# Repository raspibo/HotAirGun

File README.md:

HotAirGun
===================== 
Hot Air Solder station project
3D models for case

Project preview
=====================

<table>
<tr>
<td>

</td><td>

</td><td>

</td>
</tr>
<tr>
<td>

</td><td>

</td><td>

</td>
</tr>
</table>

License and copyright
=====================

Copyright 2017-2018 sandroxGH infomsystemsrl@gmail.com, RaspiBO info@raspibo.org

Licensed under the Apache License, Version 2.0 (the "License"); you may not use this file except in compliance with the License. You may obtain a copy of the License at http://www.apache.org/licenses/LICENSE-2.0

Unless required by applicable law or agreed to in writing, software distributed under the License is distributed on an "AS IS" BASIS, WITHOUT WARRANTIES OR CONDITIONS OF ANY KIND, either express or implied. See the License for the specific language governing permissions and limitations under the License.

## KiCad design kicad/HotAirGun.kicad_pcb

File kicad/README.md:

# Avvertenza sul caricamento dei simboli
All'apertura dello schema kicad può richiedere di sostituire i simboli dei componenti come se si riferissero a librerie obsolete.

E' consigliabile annullare l'operazione in modo che venga caricato il simbolo presente nel file cache delle librerie.

Schema preview
=====================

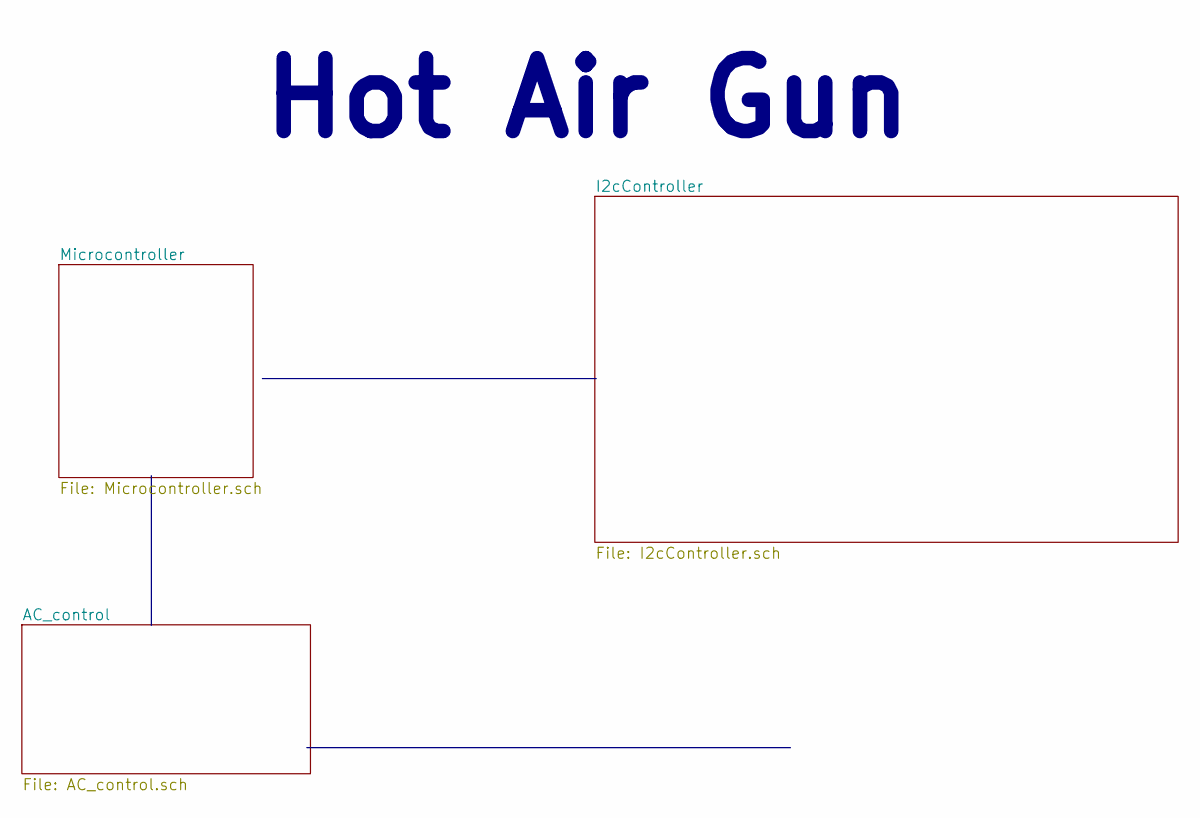
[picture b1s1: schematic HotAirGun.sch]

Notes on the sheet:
Hot Air Gun

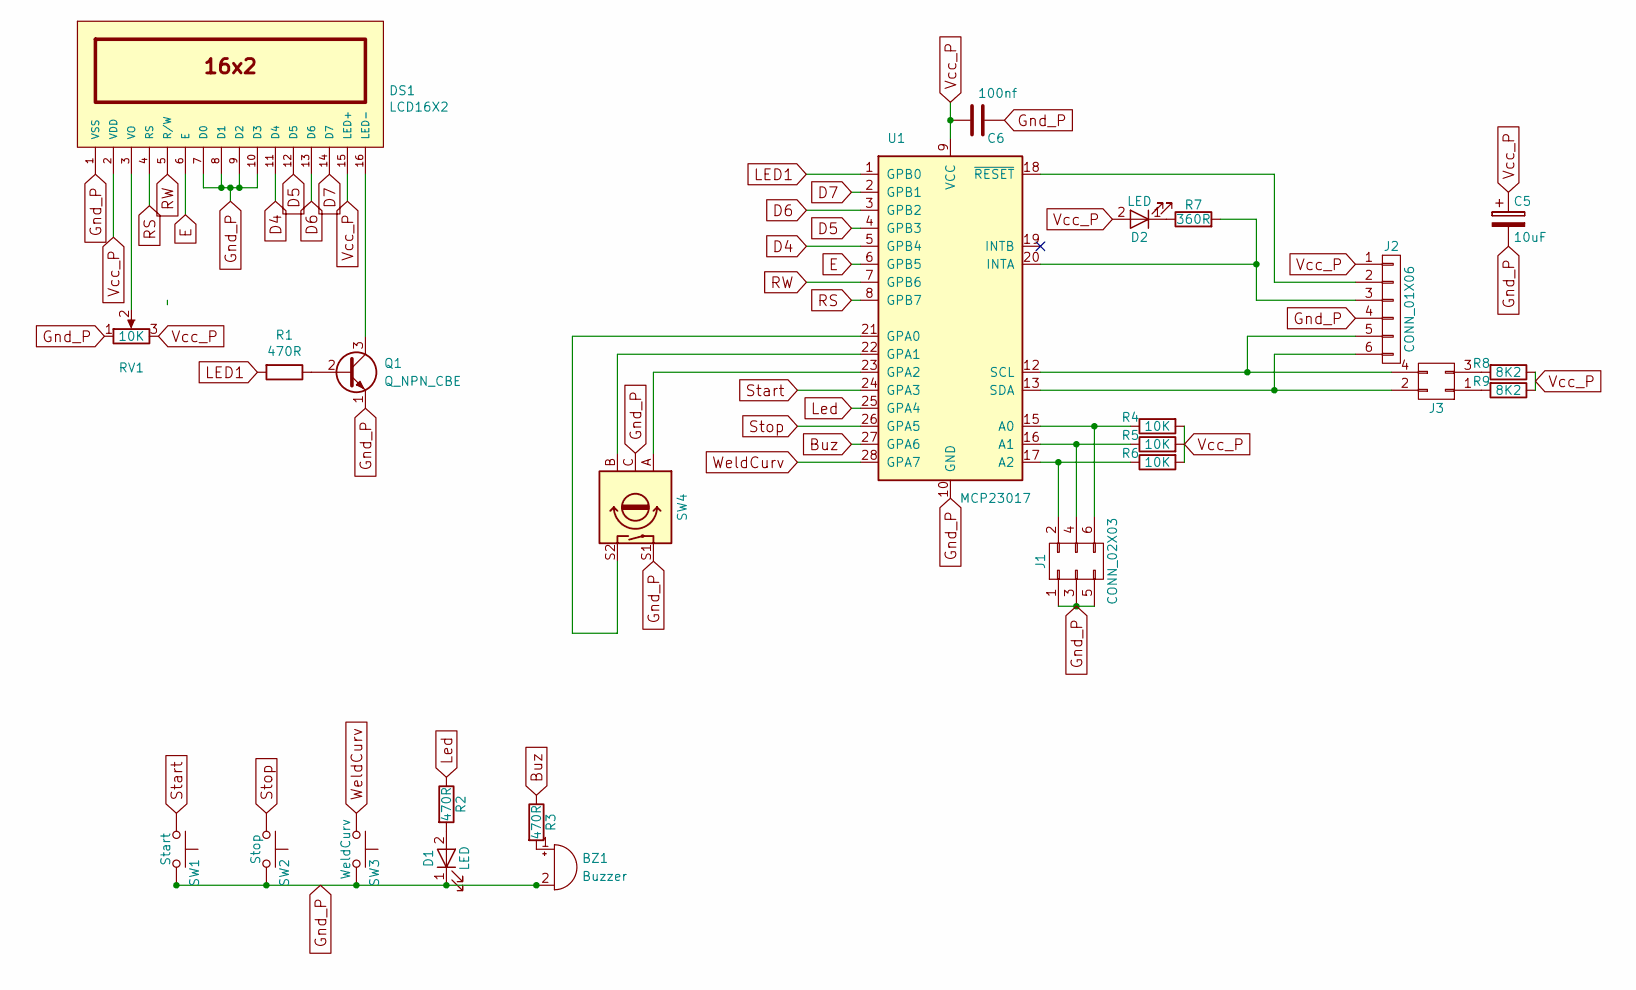
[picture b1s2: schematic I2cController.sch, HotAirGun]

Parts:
BZ1: Buzzer; Buzzer_12x9.5RM7.6
C5: 10uF; CP_Radial_D10.0mm_P5.00mm
C6: 100nf; C_0603_HandSoldering
D1, D2: LED; LED-5MM
DS1: LCD16X2; WC1602A
J1: CONN_02X03; Pin_Header_Straight_2x03
J2: CONN_01X06; Pin_Header_Straight_1x06
J3: CONN_02X02; Pin_Header_Straight_2x02
Q1: Q_NPN_CBE; TO-92_Rugged_Reverse
R1: 470R; R3
R2, R3: 470R; R_0603_HandSoldering
R4, R5, R6: 10K; R_0603_HandSoldering
R7: 360R; R_0603_HandSoldering
R8, R9: 8K2; R_0603_HandSoldering
RV1: 10K; Potentiometer_VishaySpectrol-Econtrim-Type36M
SW1: Start; SW_PUSH_SMALL
SW2: Stop; SW_PUSH_SMALL
SW3: WeldCurv; SW_PUSH_SMALL
SW4: Rotary_Encoder_Switch_V2; RotaryEncoder_Alps_EC11E-Switch_Vertical_H20mm
U1: MCP23017; DIP-28_W7.62mm_LongPads

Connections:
Buz: R3.1, U1.27 (GPA6)
D4: DS1.11 (D4), U1.5 (GPB4)
D5: DS1.12 (D5), U1.4 (GPB3)
D6: DS1.13 (D6), U1.3 (GPB2)
D7: DS1.14 (D7), U1.2 (GPB1)
E: DS1.6 (E), U1.6 (GPB5)
Gnd_P: BZ1.2 (+), C5.2, C6.1, D1.1 (K), DS1.1 (VSS), DS1.7 (D0), DS1.8 (D1), DS1.9 (D2), DS1.10 (D3), J1.1, J1.3, J1.5, J2.4, Q1.1 (E), RV1.1, SW1.2, SW2.2, SW3.2, SW4.C, SW4.S1, U1.10 (GND)
LED1: R1.2, U1.1 (GPB0)
Led: R2.1, U1.25 (GPA4)
unnamed: BZ1.1 (-), R3.2
unnamed: D1.2 (A), R2.2
unnamed: D2.1 (K), R7.1
unnamed: DS1.3 (VO), RV1.2
unnamed: DS1.16 (LED-), Q1.3 (C)
unnamed: J1.2, R6.1, U1.17 (A2)
unnamed: J1.4, R5.1, U1.16 (A1)
unnamed: J1.6, R4.1, U1.15 (A0)
unnamed: J2.2, U1.18 (~RESET)
unnamed: J2.3, R7.2, U1.20 (INTA)
unnamed: J2.5, J3.4, U1.12 (SCL)
unnamed: J2.6, J3.2, U1.13 (SDA)
unnamed: J3.1, R9.2
unnamed: J3.3, R8.2
unnamed: Q1.2 (B), R1.1
unnamed: SW4.A, U1.23 (GPA2)
unnamed: SW4.B, U1.22 (GPA1)
unnamed: SW4.S2, U1.21 (GPA0)
RS: DS1.4 (RS), U1.8 (GPB7)
RW: DS1.5 (R/W), U1.7 (GPB6)
Start: SW1.1, U1.24 (GPA3)
Stop: SW2.1, U1.26 (GPA5)
Vcc_P: C5.1, C6.2, D2.2 (A), DS1.2 (VDD), DS1.15 (LED+), J2.1, R4.2, R5.2, R6.2, R8.1, R9.1, RV1.3, U1.9 (VCC)
WeldCurv: SW3.1, U1.28 (GPA7)

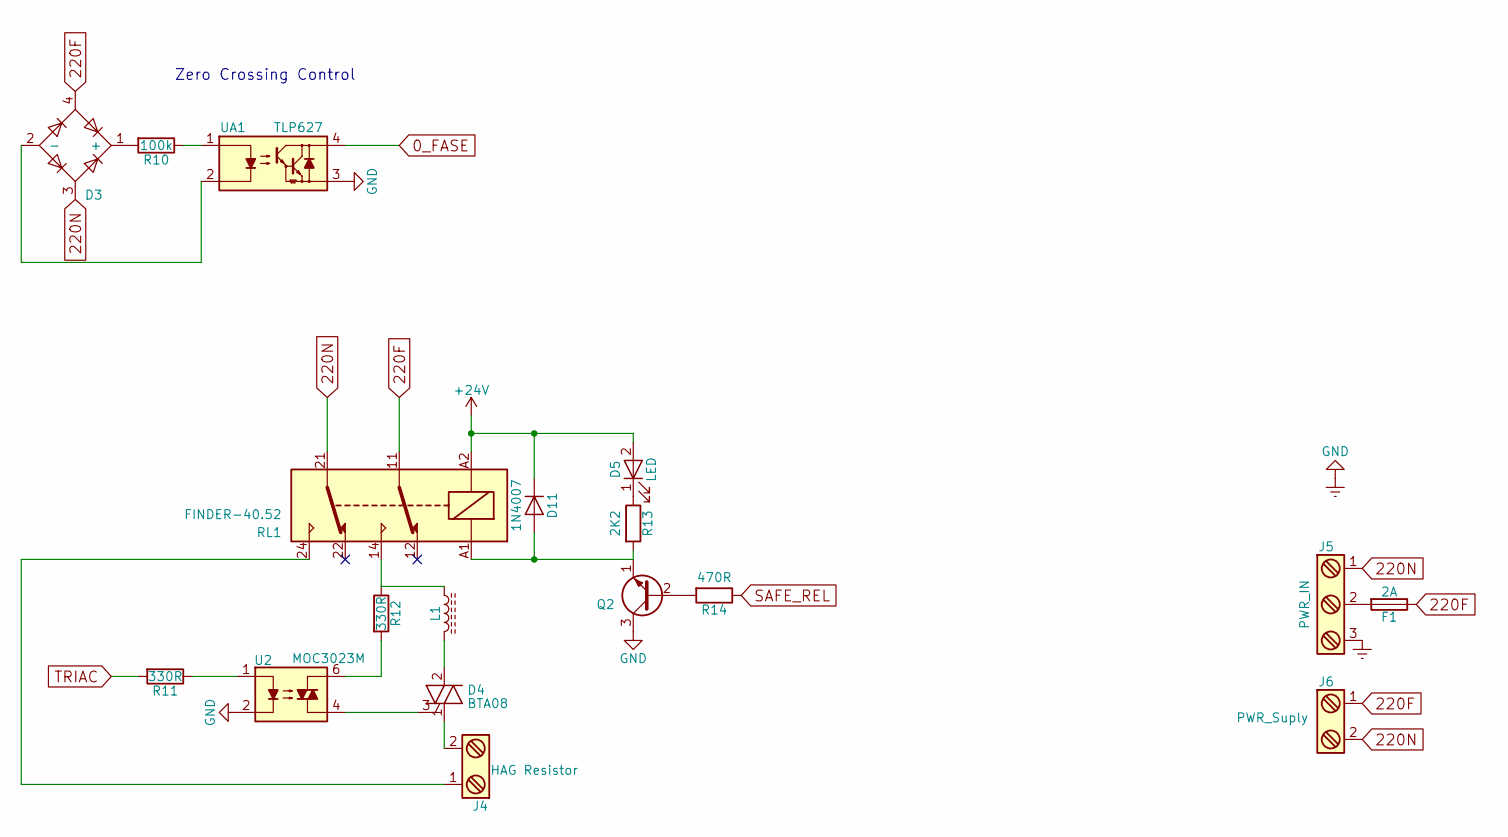
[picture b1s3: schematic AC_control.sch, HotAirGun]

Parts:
D3: D_Bridge_+-AA; Diode_Bridge_8.5
D4: BTA08; TO-220_Neutral123_Vertical
D5: LED; LED-3MM
D11: 1N4007; D_DO-35_SOD27_P7.62mm_Horizontal
F1: 2A; Fuseholder5x20_horiz_open_Schurter_0031_8201
J4: HAG Resistor; PhoenixContact_MSTBVA-G_02x5.08mm_Vertical
J5: PWR_IN; PhoenixContact_MSTBVA-G_03x5.08mm_Vertical
J6: PWR_Suply; PhoenixContact_MSTBVA-G_02x5.08mm_Vertical
L1: L_Core_Ferrite; Choke_SMD_PISR_Handsoldering_FASTRON
Q2: Q_PNP_CBE; TO-92_Rugged
R10: 100k; D4
R11: 330R; Resistor_Horizontal_RM7mm
R12: 330R; R3
R13: 2K2; R_0603_HandSoldering
R14: 470R; R_0603_HandSoldering
RL1: FINDER-40.52; Relay_SPDT_Schrack-RT1_RM5mm
U2: MOC3023M; DIP-6_W7.62mm
UA1: TLP627; DIP-4_W7.62mm

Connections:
0_FASE: UA1.4; also elsewhere on the board
220F: D3.4, F1.1, J6.1, RL1.11
220N: D3.3, J5.1, J6.2, RL1.21
+24V: D5.2 (A), D11.1 (K), RL1.A2; also elsewhere on the board
Earth: J5.3, Q2.3 (C), U2.2, UA1.3; also elsewhere on the board
unnamed: D3.1 (+), R10.2
unnamed: D3.2 (-), UA1.2
unnamed: D4.1 (A1), J4.2
unnamed: D4.2 (A2), L1.2
unnamed: D4.3 (G), U2.4
unnamed: D5.1 (K), R13.1
unnamed: D11.2 (A), Q2.1 (E), R13.2, RL1.A1
unnamed: F1.2, J5.2
unnamed: J4.1, RL1.24
unnamed: L1.1, R12.1, RL1.14
unnamed: Q2.2 (B), R14.2
unnamed: R10.1, UA1.1
unnamed: R11.1, U2.1
unnamed: R12.2, U2.6
SAFE_REL: R14.1; also elsewhere on the board
TRIAC: R11.2; also elsewhere on the board

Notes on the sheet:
Zero Crossing Control

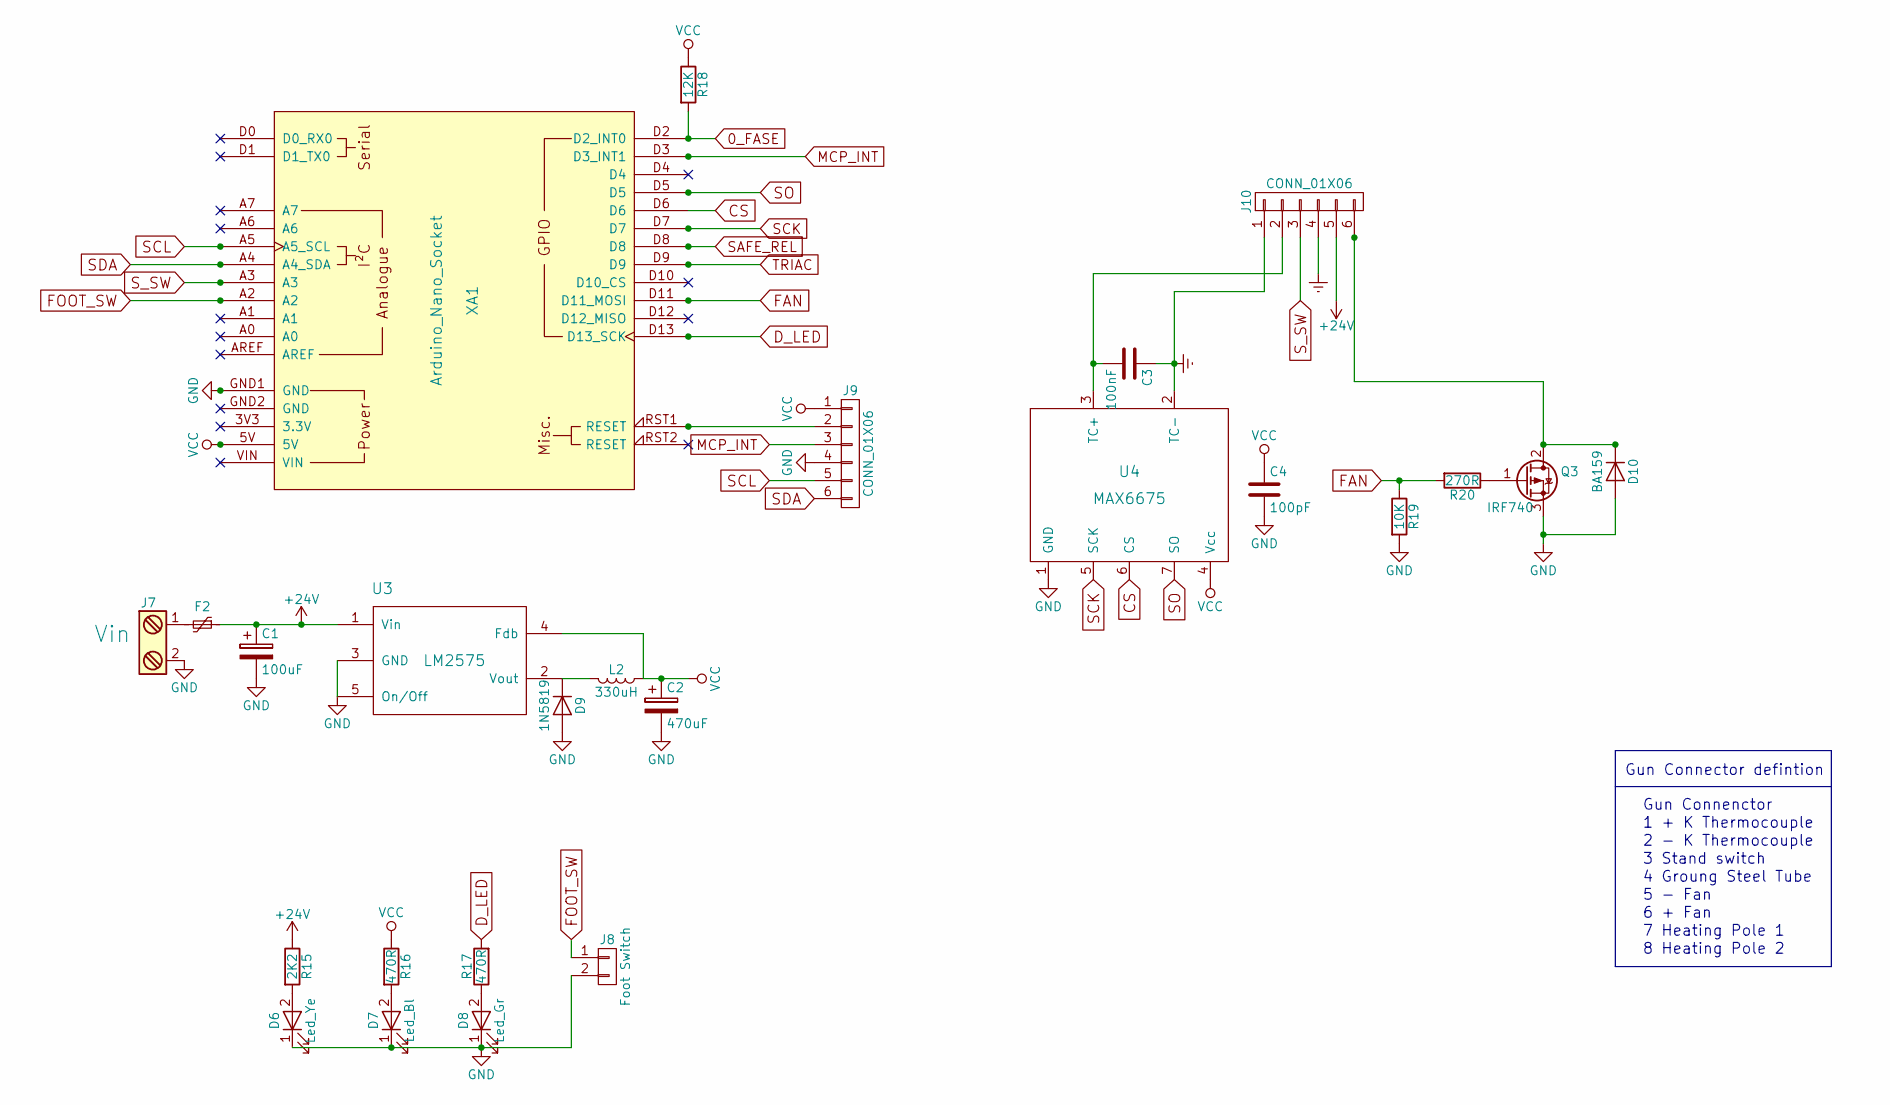
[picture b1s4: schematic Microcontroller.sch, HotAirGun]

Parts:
C1: 100uF; CP_Radial_D12.5mm_P7.50mm
C2: 470uF; CP_Radial_D12.5mm_P7.50mm
C3: 100nF; C_0603_HandSoldering
C4: 100pF; C_0603_HandSoldering
D6: Led_Ye; LED-3MM
D7: Led_Bl; LED-3MM
D8: Led_Gr; LED-3MM
D9: 1N5819; D_DO-35_SOD27_P7.62mm_Horizontal
D10: BA159; D4
F2: Polyfuse_Small; Fuseholder5x20_horiz_open_Schurter_0031_8201
J7: Vin; PhoenixContact_MSTBVA-G_02x5.08mm_Vertical
J8: Foot Switch; JACK_ALIM
J9, J10: CONN_01X06; Pin_Header_Straight_1x06
L2: 330uH; Induttanza
Q3: IRF740; TO-220_Vertical
R15: 2K2; R_0603_HandSoldering
R16, R17: 470R; R_0603_HandSoldering
R18: 12K; R_0603_HandSoldering
R19: 10K; R_0603_HandSoldering
R20: 270R; R_0603_HandSoldering
U3: LM2575; Pentawatt_Neutral_Staggered_Verical_TO220-5-T05D
U4: MAX6675; SOIC-8_3.9x4.9mm_Pitch1.27mm
XA1: Arduino_Nano_Socket

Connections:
0_FASE: R18.2, XA1.D2 (D2_INT0); also elsewhere on the board
+24V: C1.1, F2.1, J10.5, R15.1, U3.1 (Vin); also elsewhere on the board
CS: U4.6 (CS), XA1.D6
D_LED: R17.2, XA1.D13 (D13_SCK)
Earth: C1.2, C2.2, C3.1, C4.2, D6.1 (K), D7.1 (K), D8.1 (K), D9.2 (A), D10.2 (A), J7.2, J8.2, J9.4, J10.1, J10.4, Q3.3 (S), R19.2, U3.3 (GND), U3.5 (On/Off), U4.1 (GND), U4.2 (TC-), XA1.GND1 (GND); also elsewhere on the board
FAN: R19.1, R20.2, XA1.D11 (D11_MOSI)
FOOT_SW: J8.1, XA1.A2
MCP_INT: J9.3, XA1.D3 (D3_INT1)
unnamed: C3.2, J10.2, U4.3 (TC+)
unnamed: D6.2 (A), R15.2
unnamed: D7.2 (A), R16.2
unnamed: D8.2 (A), R17.1
unnamed: D9.1 (K), L2.2, U3.2 (Vout)
unnamed: D10.1 (K), J10.6, Q3.2 (D)
unnamed: F2.2, J7.1
unnamed: J9.2, XA1.RST1 (RESET)
unnamed: Q3.1 (G), R20.1
SAFE_REL: XA1.D8; also elsewhere on the board
SCK: U4.5 (SCK), XA1.D7
SCL: J9.5, XA1.A5 (A5_SCL)
SDA: J9.6, XA1.A4 (A4_SDA)
SO: U4.7 (SO), XA1.D5
S_SW: J10.3, XA1.A3
TRIAC: XA1.D9; also elsewhere on the board
VCC: C2.1, C4.1, J9.1, L2.1, R16.1, R18.1, U3.4 (Fdb), U4.4 (Vcc), XA1.5V

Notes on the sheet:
Gun Connenctor
1 + K Thermocouple
2 - K Thermocouple
3 Stand switch
4 Groung Steel Tube
5 - Fan
6 + Fan
7 Heating Pole 1
8 Heating Pole 2
Gun Connector defintion

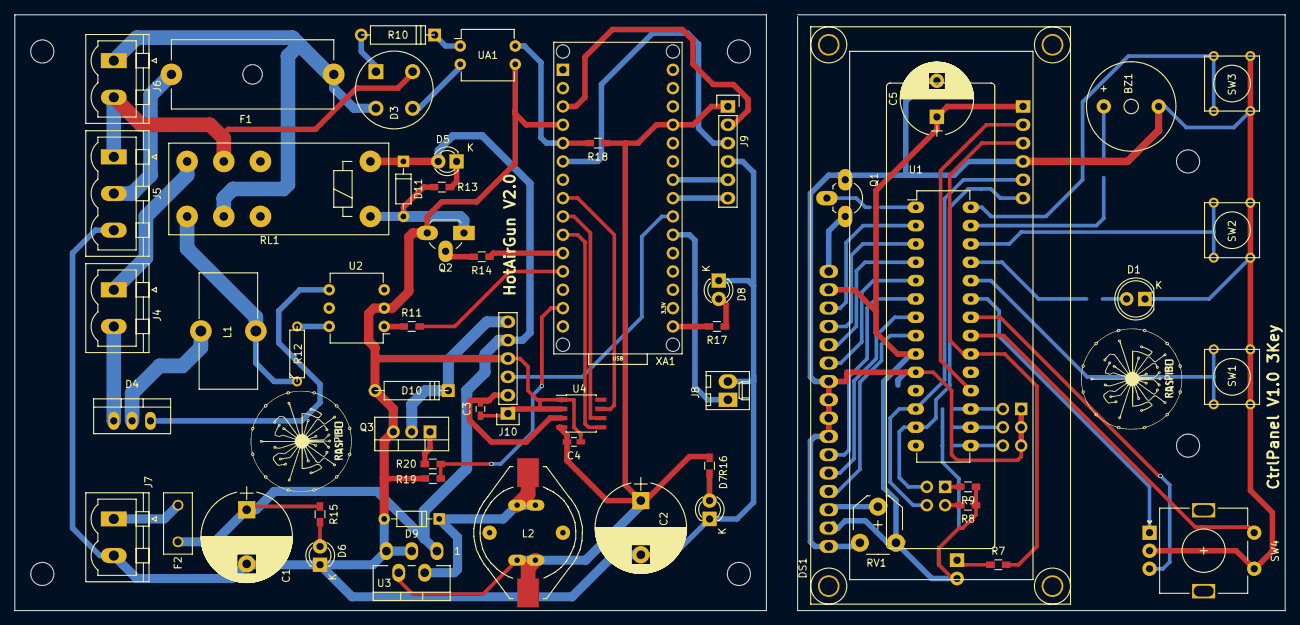
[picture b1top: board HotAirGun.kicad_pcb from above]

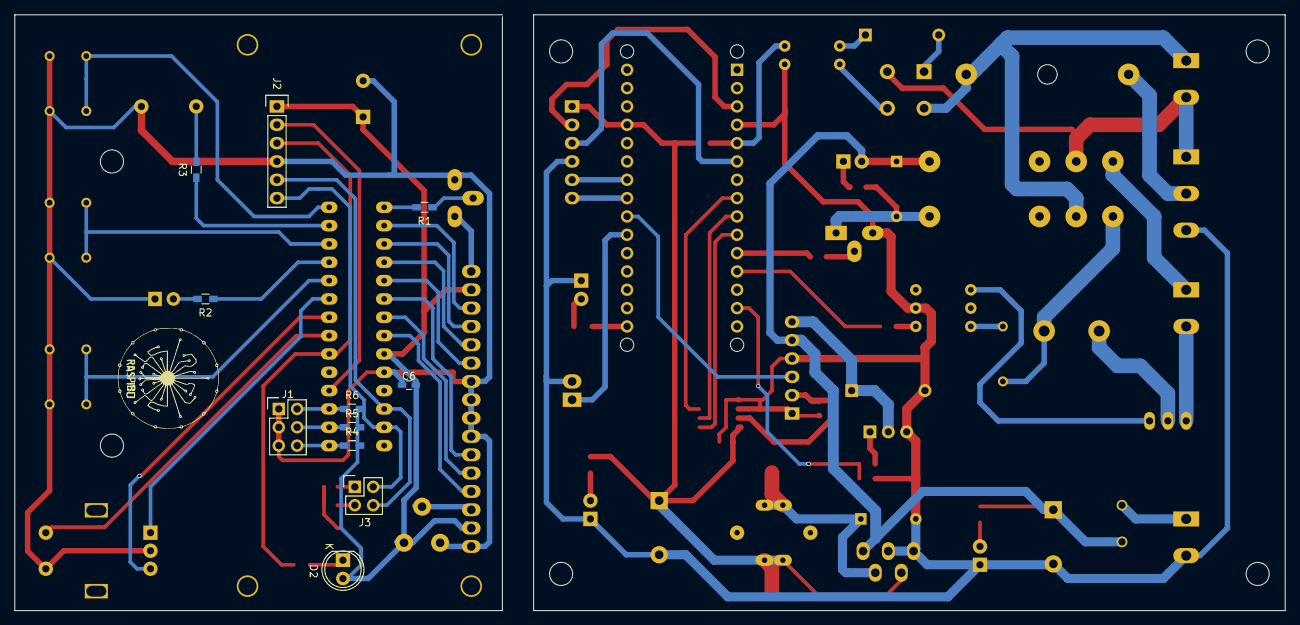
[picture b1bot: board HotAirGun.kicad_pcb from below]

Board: 2 copper layers, 176.0 x 82.5 mm, 68 parts (11 on the bottom side), 74 nets.

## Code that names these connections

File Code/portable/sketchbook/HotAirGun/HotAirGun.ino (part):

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#define SO			5	//MAX6675 signal serial out aka MISO on SPI
#define CS			6	//MAX6675 signal Chip select
#define SCK			7	//MAX6675 signal clock
#define GATE		9 	//TRIAC gate
#define EMERG_RELAY 8	//Emergency and power relay
#define P_FAN_PWM	11  //Define pin D10 for pwm signal for gun
#define _STARTSTOP	12  //Pin used for activation of hot air production (also used for magnetic sensor on gun)
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		 contr.buzz(200, 1500);
	 }	 
	 if(( TempGunApp < Target2) && LiftUp){
		if(( WeldCurv == 1) && TempInDelt ) {
		  TempGunApp++;
		  contr.buzz(100, 1500);
		}
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    AirFlowApp = 100;
    //Serial.println("Auto Power OFF");
    if (ActTemp <= TStop) {
      AirFlow = 0;  //when air on gun is lower than TStop temp cut off pwm on fan
      OCR2A = 0;
      Serial.println("Fan stop");
      delay(500);
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
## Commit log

2017-03-03 Readme update
2017-03-03 Update with license
2017-03-03 Update with images
2017-03-03 update text
2017-03-05 Create 3D
2017-03-05 Rename Frontale.stl to 3d/Frontale.stl
2017-03-05 Rename Piedini scheda.stl to 3D/Piedini scheda.stl
2017-03-05 Rename Retro.stl to 3D/Retro.stl
2017-03-05 Rename colonna 130.stl to 3D/colonna 130.stl
2017-03-05 Rename colonna 106.stl to 3D/colonna 106.stl
2017-03-05 Rename Tasto.stl to 3D/Tasto.stl
2017-03-05 Rename 3d/Frontale.stl to 3D/Frontale.stl
2017-03-05 Rename Sostegno Induttanza.stl to 3D/Sostegno Induttanza.stl
2017-03-05 Rename Staffa alim.stl to 3D/PWSuplSupp.stl
2017-03-05 Rename Frontale.stl to Front.stl
2017-03-05 Rename Piedini scheda.stl to BoardFix.stl
2017-03-05 Rename Retro.stl to Back.stl
2017-03-05 Rename Sostegno Induttanza.stl to CoilSupport.stl
2017-03-05 Rename Tasto.stl to Key.stl
2017-03-05 Rename colonna 106.stl to Coulom106.stl
2017-03-05 Rename colonna 130.stl to Coulom130.stl
2017-03-05 Rename HotAirGun.c to Code/HotAirGun.c
2017-03-05 Rename HotAirGun.hex to Code/HotAirGun.hex
2017-03-05 Create Pct
2017-03-05 Rename Pct to Pict/Pct
2017-03-05 Create FIle
2017-03-29 Pubblicata lista materiale indicata da @sandroxGH per iniziare la sperimetazione
2017-03-30 remove duplicate line
2017-03-31 Import schema e conversione manuale in formato kicad, i componenti non disponibili nelle librerie di default di kicad sono stati sostituiti con rettangoli tratteggiati in attesa di conferma
2017-03-31 Rename files per uniformare a nome progetto
2017-03-31 Aggiornamento componenti e inclusione nell'archivio del cache libreria
2017-03-31 Modifica dimensione pagina foglio schema elettrico settato A4 per migliorare la stampa, aggiornamento informazioni sul foglio
2017-03-31 Aggiunto README.md con avvertenze sulla conversione automatica dei simboli
2017-04-01 Modifica README.md, pubblicazione schemi
2017-04-01 Eliminato resize immagine
2017-04-01 Pubblicazione schemi con appoggio su rawgit
2017-04-06 Add files via upload
    Codice test Arduino
2017-04-06 Delete FIle
    Pulizia nuova versione
2017-04-06 Delete SCH.pdf
    Pulizia nuova versione
2017-04-06 Delete PCB.pdf
    Pulizia nuova versione
2017-04-06 Delete PCB.jpg
    Pulizia nuova versione
2017-04-06 Delete SCH.jpg
    Pulizia nuova versione
2017-04-06 Create PinOut.txt
    Promemoria per assegnazione pin
2017-04-10 Schema aggiornato con arduino nano
2017-05-08 New code with display and menu
2017-05-20 Change of setupInterruptPin from CHANGE to FALLING
2017-05-20 Change pinout for encoder
2017-09-13 Update schematics plot
    Align plots to kicad schematics for preview and print without kicad
2017-09-13 Update link for schematic preview
2017-09-14 potDivider var for scroll sensibility regulation
    Add of potDivider variable make a regulation of sensibility of encoder.
    Functional in case of high speed encoder or encoder with low precison.
2017-09-14 Improve materials settings
    Add welding temperature for plastic masterials.
    Ref: https://www.bestmaterials.com/PDF_Files/BAK-Plastic-Welding2.pdf
2017-09-17 New function TempCurve
    Implement temperature cycle to follow datasheet temperature cycle for welding of specific components
2017-09-18 AutoOFFTime setting in menu and some var name repl
    Adding function in menu for AutoOffTime adjst with encoder and save to eeprom (2 bytes).
    Some var name adjust with wrong name after text replace.
2017-09-20 INT0 handler use zero cross signal for PID base
    handler for INT0 interrupt, high priority interrupt, tested with logic analyzer
    react in 3.2usec with toglle of pin
    Hardware TIP resistor pullup is required for D2 and D3 even interrupt is not handled correctly
    some typo correction and comment corrections
2017-09-20 Code indent and typo correction
2017-09-21 Addi comments and typo corrections
2017-09-21 Pwm signl on pin D10 for fan control
    Add PWM control on pin D10 for fan contol, the frequncy of pwm have to be checked if corrected.
    Implent of pwn off when auto off is active.
2017-09-22 opTime decrement in interrupt phase routine
    assure opTime decrement in every condition.
    added also a exit(0) when autoshutdown occur
2017-09-22 Change handling of MCP23017 interrupts
    They are cheched every loop and other functions are handled if buttons and encoder events
    are already handled.
2017-09-22 Replace wrong D_AutoOffTime var with AutoOffTime
    Correction for auto shutdown time calculation.
    Some Serial print and debug messages.
2017-09-25 Schematic update pullup for int pin
2017-09-25 Multiple sheet schematic
    Change schematic to multiple sheet format
2017-09-25 Add lib cache and rescue
2017-09-25 Add Gun image to general schematic
2017-09-25 Plot schematics update
2017-09-25 Change pwm frequency for fan
2017-09-27 Introduction of function PID from V1 branch
    Reuse of PID function from V1 branch with variable definitions
2017-10-01 Change interrupt handling priority
    Assure continuous handling of pid recalc in case of continuous int1 events
2017-10-01 Autoindent of code
2017-10-02 Airflow seto to max when AutoOff mode is active
2017-10-03 Timer register names
    add comments to timer registers
2017-10-03 Use timer2 for air flow pwm
    timer 2 is 8 bit counter based, timer1 is more accurate and in future used for triac
2017-10-04 add register description for timer2
2017-10-10 Config TIMER1 and interrupt for TRIAC driving
    Reconfiguration of TIMR1 for overflow interrupt and pulse generation for triac.
    At zero crossing event timer duration is recalculated
    TCNT_timer=63060+Pid_Res;
    at the first overflow new value is set for low duration pulse
    TCNT1H = 0xFF;
    TCNT1L = 0xFF - PULSE;
2017-10-10 TCNT_timer calculation from interrupt routine to PID
2017-10-10 Some adjust and max6675 basic handler
2017-10-19 MAXX6675 corrections and error for chip unconneted
    After installation of real chip, code require correction
    Add of chip disconnetion handling checking D1 bit. See datasheet.
2017-10-24 Schematic update
2017-11-01 Modified the Kicad schematic adding the reset to I2c controller
2017-11-01 added step-down circuit
2017-11-03 Check for empty eeprom and write default values
    If all eeprom cells are equal to zero, default values will be written,
    Also default values set for KP KI KD
2017-11-03 Some default values change
2017-11-05 Emergency and error function handler
    Some controls for thermocuople and zero cross circuit error detection and
    shutdown.
    Assigned arbitrary pin to emergency relay to be confirmed.
2017-11-06 Introducing var TempGunApp and AirFlowApp
    New vars for start and stop cycle used when weld cycle is not active
2017-11-06 Add Relay handling on start and stop
2017-11-09 Start and stop function revisited
    New function for start and stop button.
    Start sequence:
    - Fan start
    - Wait 2 sec
    - Relay On
    - Start Triac activation
2017-11-10 Pin definition reordering
2017-11-10 Add handler for tilt sensor
2017-11-10 Startstop revision
    In previous commit STARTSTOP was associated to phisical pin status.
    Now if STARTSTOP macro is defined phisical pin is also usable for guns with magnetic sensor.
    Else if STARTSTOP is undef 2 buttons of cross keyboard up and down are used as start and stop buttons.
2017-11-10 Update vars order and descriptions
2017-11-13 Update the PinOut file. PID variable can be changed from panel.
2017-11-13 Update the schematic with the safety relays for 220V. Microcontroller page now is connect with the grid.
2017-11-16 Replaced version before merge
2017-11-16 Reduce some pic resolution. Update PDF schematic.
2017-11-16 Added simulator picture.
2017-11-16 Umpate Picture
2017-11-19 some ver reduction for memory optimizations, negative autooff time, unused comments deletion
2017-11-19 Some minimal changes
2017-11-20 Manual conflict conversion. Some tests rquired
2018-12-09 Replace RawGit with jsDelivr
2018-12-31 New PCB version with smd component Added plot folder with gerber file
2019-02-19 Update with new PCB version
    Kicad schematic and pcb layout correction on Mosfet and Triac footprint.
2019-03-03 Fan control improvement
    Reduced the PWM frequency from 15KHz to 300Hz for a better rpm control.
    Also possible change the power supply from 12V to 24V changing the 7805 to a step down regulator board.
2019-03-21 Implementation of foot switch and Welding curve
    If selected the WLC with the footswitch can give the start of the
    welding curve
2019-03-21 Kicad project mistake correction
2019-04-03 Add some comments to vars
2019-04-04 Add some comments
2019-04-04 Add CtrlPanel lib
2019-04-04 Correct typo error
2019-05-07 New STL file for 3D printer housing
2019-05-08 Fixing support modification
2019-05-18 3D model update
2019-05-24 Added C5 bypass capacitor
2019-05-24 Added C6 bypass capacitor
2019-06-17 Frame modification
    Some adjustment to the rear part height and column 123
    Added some note on KiCad project
2019-06-20 added mounting note
2019-06-20 Rename MountingNote.md to README.md
2019-06-24 Add V2 photos
2019-06-24 Update Readme with new photos
2019-07-04 Comment of unused vars
2019-07-04 Safe temp tstop to var default to 50C for summer time
2019-07-04 Update display with temp to 0 afet stop airflow
2019-07-04 Convert fixed temp to Tstop var
2019-07-04 Detach optime form pid calc
2019-07-04 Optime visualization correction
2019-07-31 Add link to raspibo wiki
